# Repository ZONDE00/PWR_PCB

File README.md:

# GS_PCB
Power delivery PCB design files

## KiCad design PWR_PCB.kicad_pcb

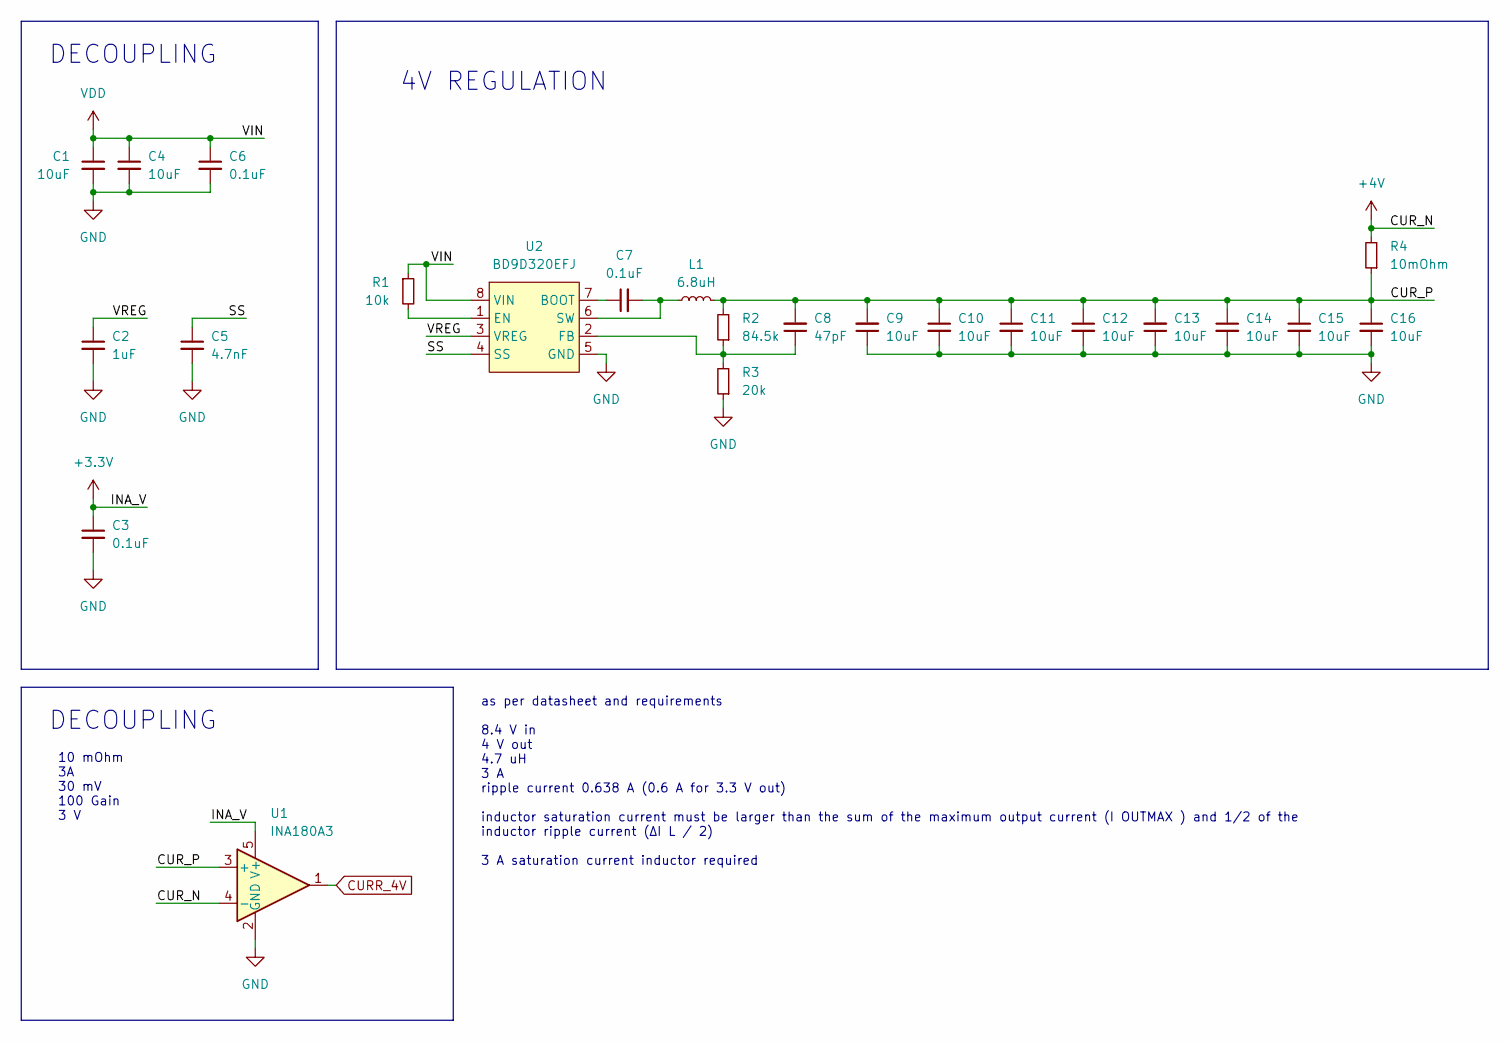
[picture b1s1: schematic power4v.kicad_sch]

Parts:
C1, C4, C9, C10, C11, C12, C13, C14, C15, C16: 10uF; C_0805_2012Metric
C2: 1uF; C_0603_1608Metric
C3, C6, C7: 0.1uF; C_0402_1005Metric
C5: 4.7nF; C_0402_1005Metric
C8: 47pF; C_0402_1005Metric
L1: 6.8uH; HM72L-06306R8
R1: 10k; R_0402_1005Metric
R2: 84.5k; R_0402_1005Metric
R3: 20k; R_0402_1005Metric
R4: 10mOhm; 0508
U1: INA180A3; SOT-23-5
U2: BD9D320EFJ; HSOP-8-1EP_3.9x4.9mm_P1.27mm_EP2.41x3.1mm

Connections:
3V3: C3.1, U1.5 (V+); also elsewhere on the board
4V: R4.2, U1.4 (-); also elsewhere on the board
/POWER_4V/CUR_P: C8.2, C9.2, C10.1, C11.1, C12.1, C13.2, C14.1, C15.1, C16.1, L1.2, R2.2, R4.1, U1.3 (+)
/POWER_4V/SS: C5.1, U2.4 (SS)
/POWER_4V/VREG: C2.1, U2.3 (VREG)
CURR_4V: U1.1; also elsewhere on the board
GND: C1.2, C2.2, C3.2, C4.2, C5.2, C6.2, C9.1, C10.2, C11.2, C12.2, C13.1, C14.2, C15.2, C16.2, R3.1, U1.2 (GND), U2.5 (GND), U2.9 (GND); also elsewhere on the board
unnamed: C7.1, U2.7 (BOOT)
unnamed: C7.2, L1.1, U2.6 (SW)
unnamed: C8.1, R2.1, R3.2, U2.2 (FB)
unnamed: R1.2, U2.1 (EN)
VDD: C1.1, C4.1, C6.1, R1.1, U2.8 (VIN); also elsewhere on the board

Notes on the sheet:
4V REGULATION
as per datasheet and requirements 8.4 V in 4 V out 4.7 uH 3 A ripple current 0.638 A (0.6 A for 3.3 V out) inductor saturation current must be larger than the sum of the maximum output current (I OUTMAX ) and 1/2 of the inductor ripple current (∆I L / 2) 3 A saturation current inductor required
DECOUPLING
10 mOhm 3A 30 mV 100 Gain 3 V

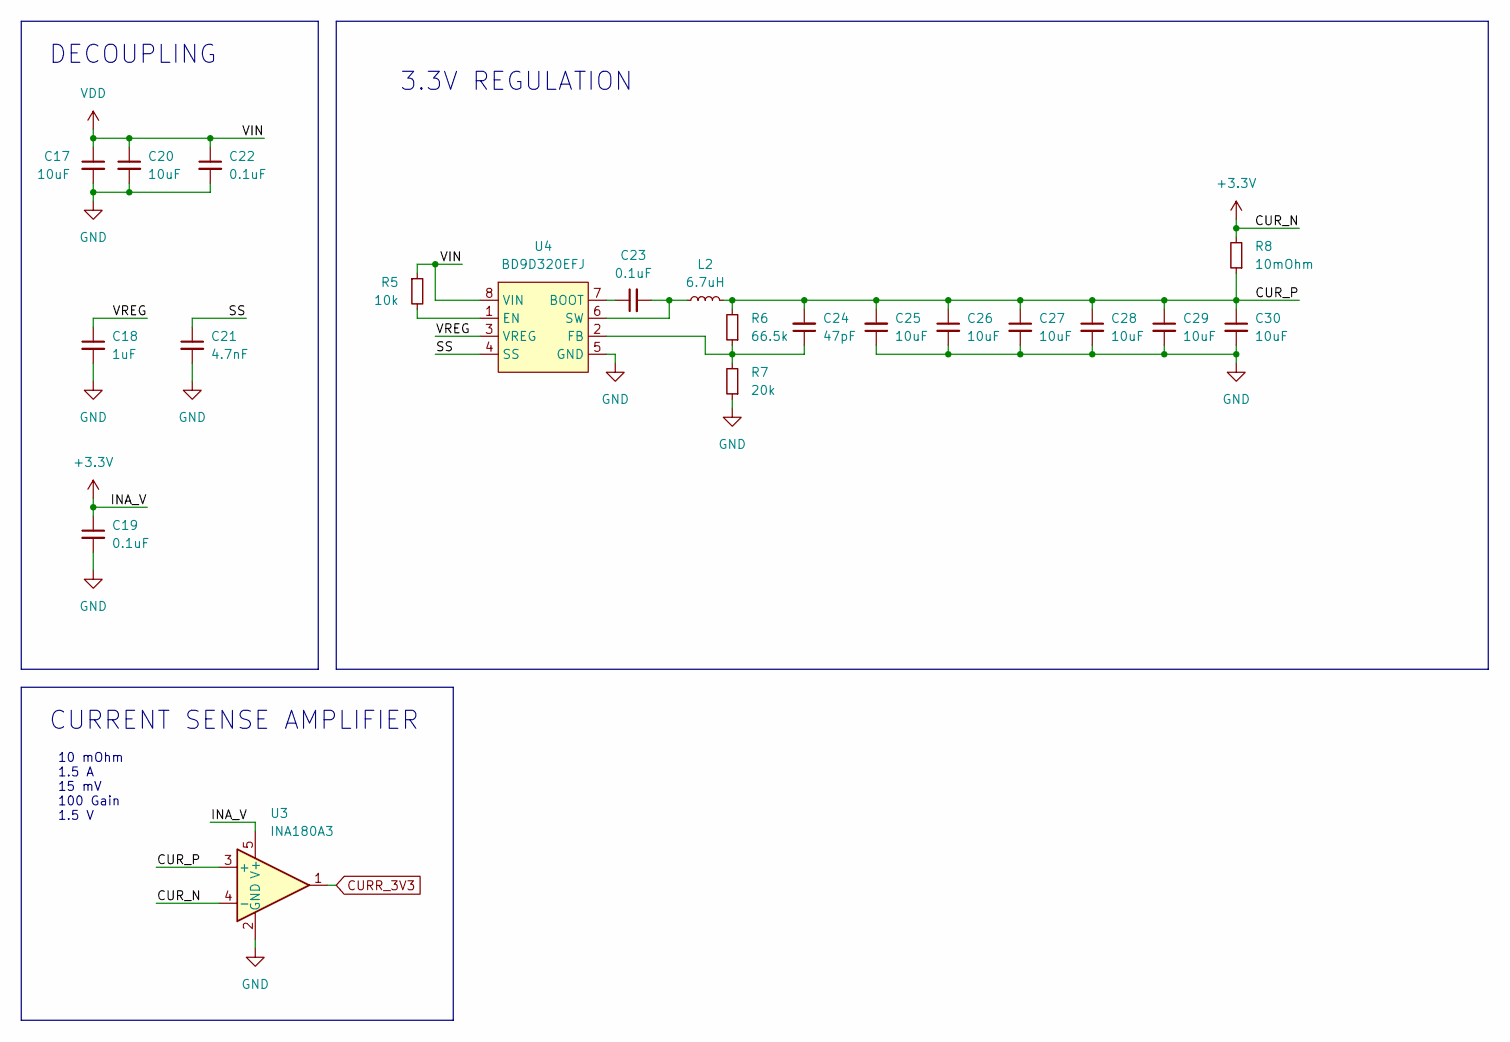
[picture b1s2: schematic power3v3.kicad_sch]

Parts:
C17, C20, C25, C26, C27, C28, C29, C30: 10uF; C_0805_2012Metric
C18: 1uF; C_0603_1608Metric
C19, C22, C23: 0.1uF; C_0402_1005Metric
C21: 4.7nF; C_0402_1005Metric
C24: 47pF; C_0402_1005Metric
L2: 6.7uH; HM72L-06306R8
R5: 10k; R_0402_1005Metric
R6: 66.5k; R_0402_1005Metric
R7: 20k; R_0402_1005Metric
R8: 10mOhm; 0508
U3: INA180A3; SOT-23-5
U4: BD9D320EFJ; HSOP-8-1EP_3.9x4.9mm_P1.27mm_EP2.41x3.1mm

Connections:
3V3: C19.1, R8.2, U3.4 (-), U3.5 (V+); also elsewhere on the board
/POWER_3V3/CUR_P: C24.2, C25.2, C26.1, C27.1, C28.1, C29.1, C30.1, L2.2, R6.2, R8.1, U3.3 (+)
/POWER_3V3/SS: C21.1, U4.4 (SS)
/POWER_3V3/VREG: C18.1, U4.3 (VREG)
CURR_3V3: U3.1; also elsewhere on the board
GND: C17.2, C18.2, C19.2, C20.2, C21.2, C22.2, C25.1, C26.2, C27.2, C28.2, C29.2, C30.2, R7.1, U3.2 (GND), U4.5 (GND), U4.9 (GND); also elsewhere on the board
unnamed: C23.1, U4.7 (BOOT)
unnamed: C23.2, L2.1, U4.6 (SW)
unnamed: C24.1, R6.1, R7.2, U4.2 (FB)
unnamed: R5.2, U4.1 (EN)
VDD: C17.1, C20.1, C22.1, R5.1, U4.8 (VIN); also elsewhere on the board

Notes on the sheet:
10 mOhm 1.5 A 15 mV 100 Gain 1.5 V
CURRENT SENSE AMPLIFIER
3.3V REGULATION
DECOUPLING

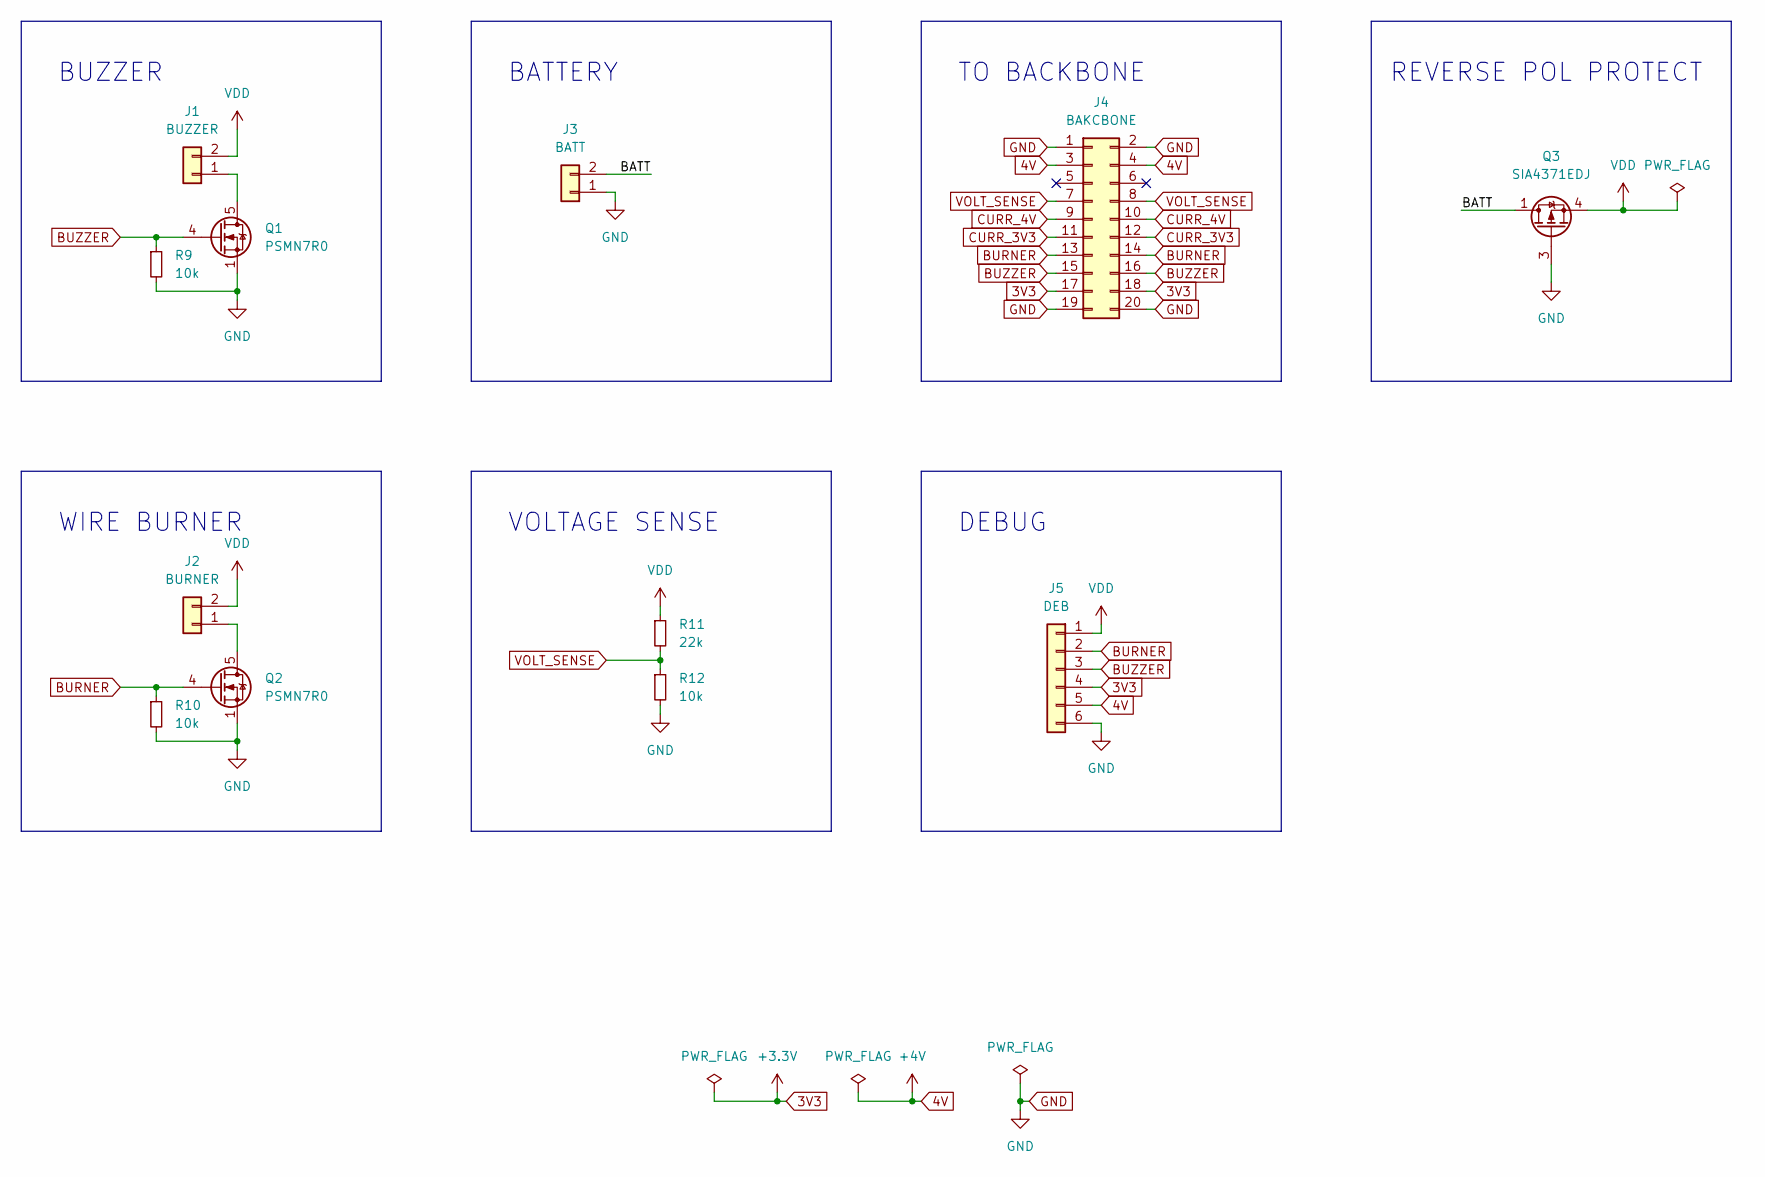
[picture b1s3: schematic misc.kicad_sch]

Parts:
J1: BUZZER; PinHeader_1x02_P2.54mm_Vertical
J2: BURNER; PinHeader_1x02_P2.54mm_Vertical
J3: BATT; PinHeader_1x02_P2.54mm_Vertical
J4: BAKCBONE; PinSocket_2x10_P2.54mm_Horizontal
J5: DEB; PinSocket_1x06_P2.54mm_Horizontal
Q1, Q2: PSMN7R0; LFPAK33
Q3: SIA4371EDJ; Vishay_PowerPAK_SC70-6L_Single
R9, R10: 10k; R_0402_1005Metric
R11: 22k; R_0603_1608Metric
R12: 10k; R_0603_1608Metric

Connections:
3V3: J4.17, J4.18, J5.4; also elsewhere on the board
4V: J4.3, J4.4, J5.5; also elsewhere on the board
/MISC/BATT: J3.2, Q3.1 (D)
BURNER: J4.13, J4.14, J5.2, Q2.4 (G), R10.1
BUZZER: J4.15, J4.16, J5.3, Q1.4 (G), R9.1
CURR_3V3: J4.11, J4.12; also elsewhere on the board
CURR_4V: J4.9, J4.10; also elsewhere on the board
GND: J3.1, J4.1, J4.2, J4.19, J4.20, J5.6, Q1.1 (S), Q1.2 (S), Q1.3 (S), Q2.1 (S), Q2.2 (S), Q2.3 (S), Q3.3 (G), R9.2, R10.2, R12.2; also elsewhere on the board
unnamed: J1.1, Q1.5 (D)
unnamed: J2.1, Q2.5 (D)
VDD: J1.2, J2.2, J5.1, Q3.4 (S), R11.1; also elsewhere on the board
VOLT_SENSE: J4.7, J4.8, R11.2, R12.1

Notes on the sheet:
BUZZER
REVERSE POL PROTECT
DEBUG
WIRE BURNER
BATTERY
VOLTAGE SENSE
TO BACKBONE

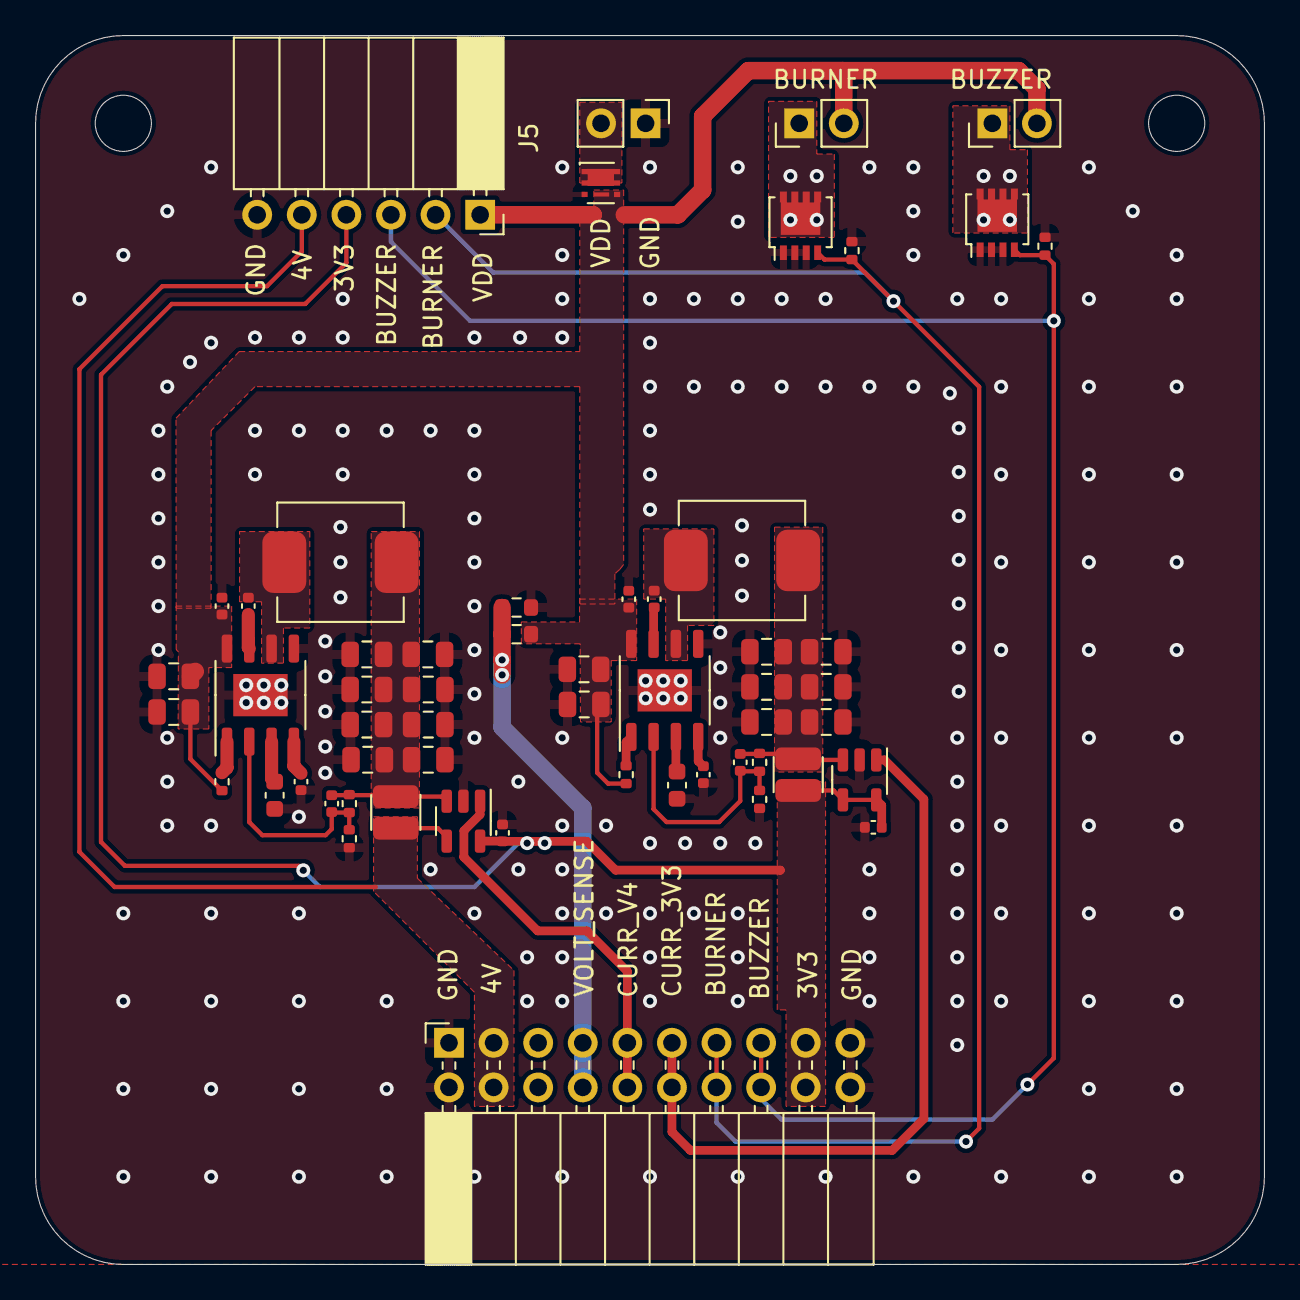
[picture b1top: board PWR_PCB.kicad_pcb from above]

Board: 2 copper layers, 70.0 x 70.0 mm, 58 parts (0 on the bottom side), 26 nets.

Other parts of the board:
H1, H2: MountingHole; MountingHole_3.2mm_M3

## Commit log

2022-09-22 init
2022-09-22 Added readme
2022-09-22 First version for PCB
2022-09-24 Added debug things
2022-09-24 Reverse polarity protection
2022-09-25 Changed ressistor values
